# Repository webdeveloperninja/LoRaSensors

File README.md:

# Remote Monitoring Arduino Shield
## LoRa Connectivity
## Sensors
- Temperature
- Humidity
- Air Particulate
- Ambient Light

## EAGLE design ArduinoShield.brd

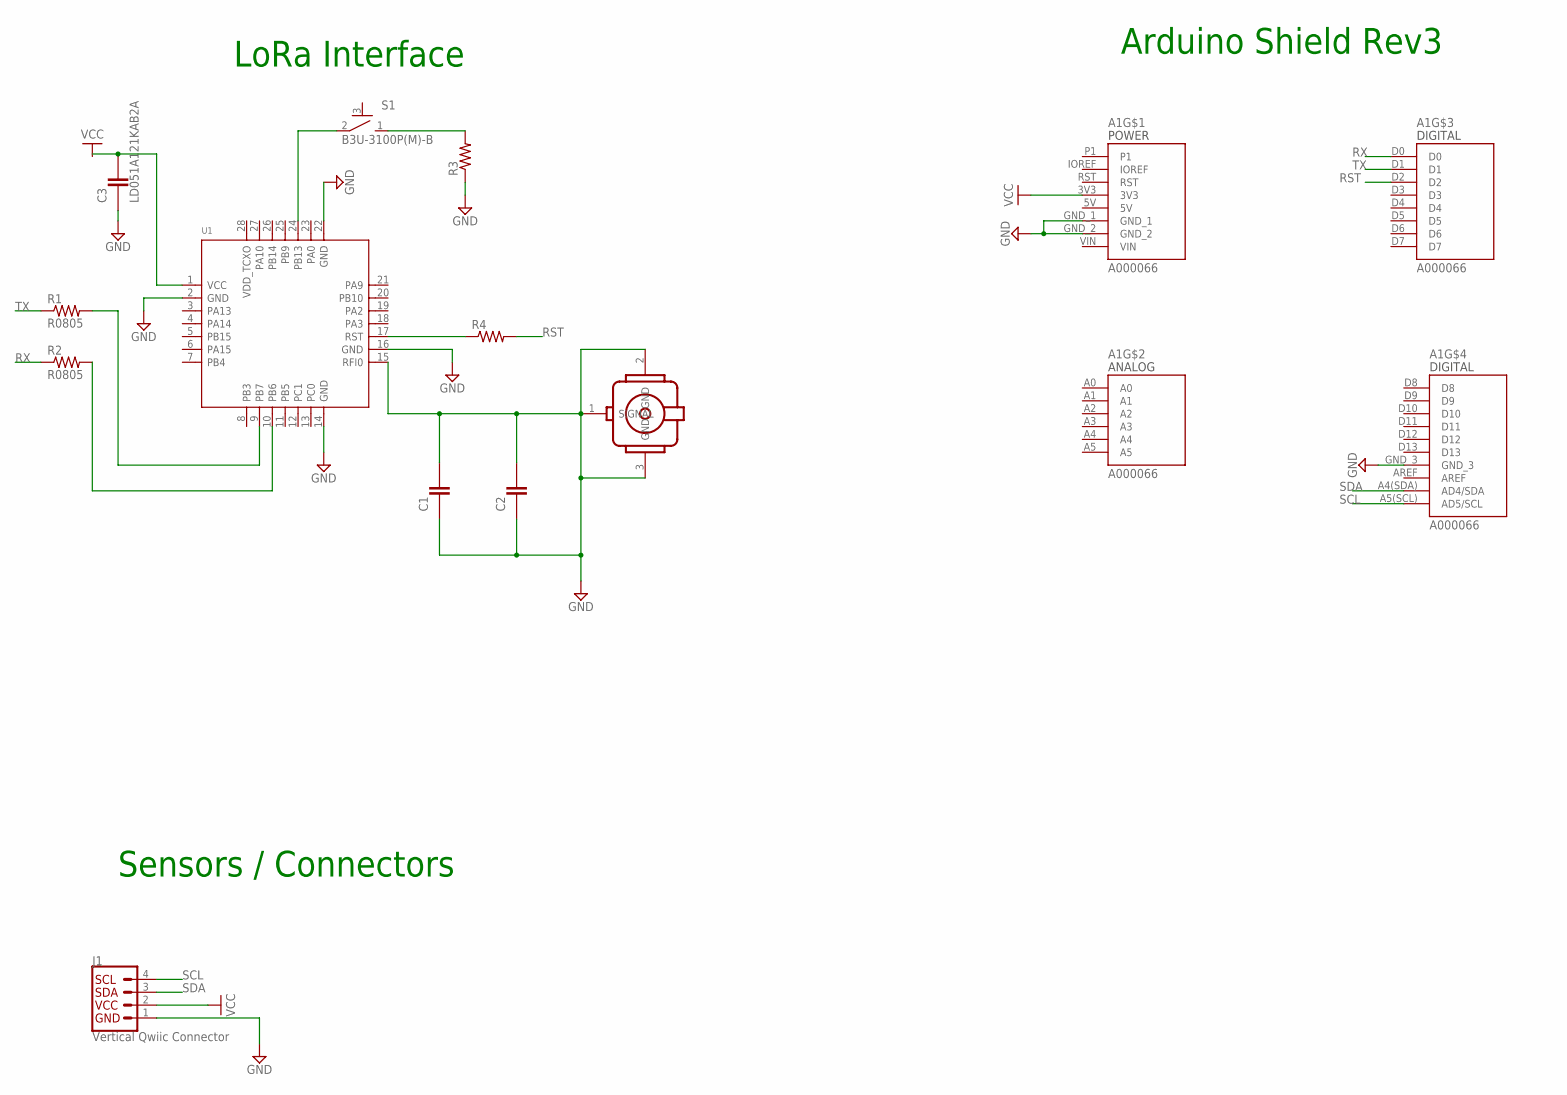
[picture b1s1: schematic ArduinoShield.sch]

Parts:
A1: A000066; ARDUINO_A000066
C1, C2, C3: LD051A121KAB2A; CAPC2012X140N
J1: Vertical Qwiic Connector; JST04_1MM_VERT
R1, R2: R0805; RESC2012X65N
R3, R4: 2-2176053-0; RESC2012X65N
S1: B3U-3100P(M)-B
U1: MODULE_LORA_E5; MODULE28P-1.25-12X12X2.5MM
U$1: U.FL-R-SMT-1(60)

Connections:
5V: A1.5V
GND: A1.GND_1, A1.GND_2, A1.GND_3, C1.1, C1.2, C2.1, C2.2, J1.1, R3.1, U1.2 (GND), U1.14 (GND), U1.15 (RFI0), U1.16 (GND), U1.22 (GND), U$1.1 (SIGNAL), U$1.2 (GND), U$1.3 (GND)
unnamed: R2.2, U1.10 (PB6)
unnamed: R1.2, U1.9 (PB7)
unnamed: R4.1, U1.17 (RST)
unnamed: S1.2 (1), U1.24 (PB13)
unnamed: R3.2, S1.1 (2)
RST: A1.D2, R4.2
RX: A1.D0, R2.1
SCL: A1.A5(SCL) (AD5/SCL), J1.4
SDA: A1.A4(SDA) (AD4/SDA), J1.3
TX: A1.D1, R1.1
VCC: A1.3V3, C3.2, J1.2, U1.1 (VCC)
VIN: A1.VIN

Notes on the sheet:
Arduino Shield Rev3
LoRa Interface
Sensors / Connectors

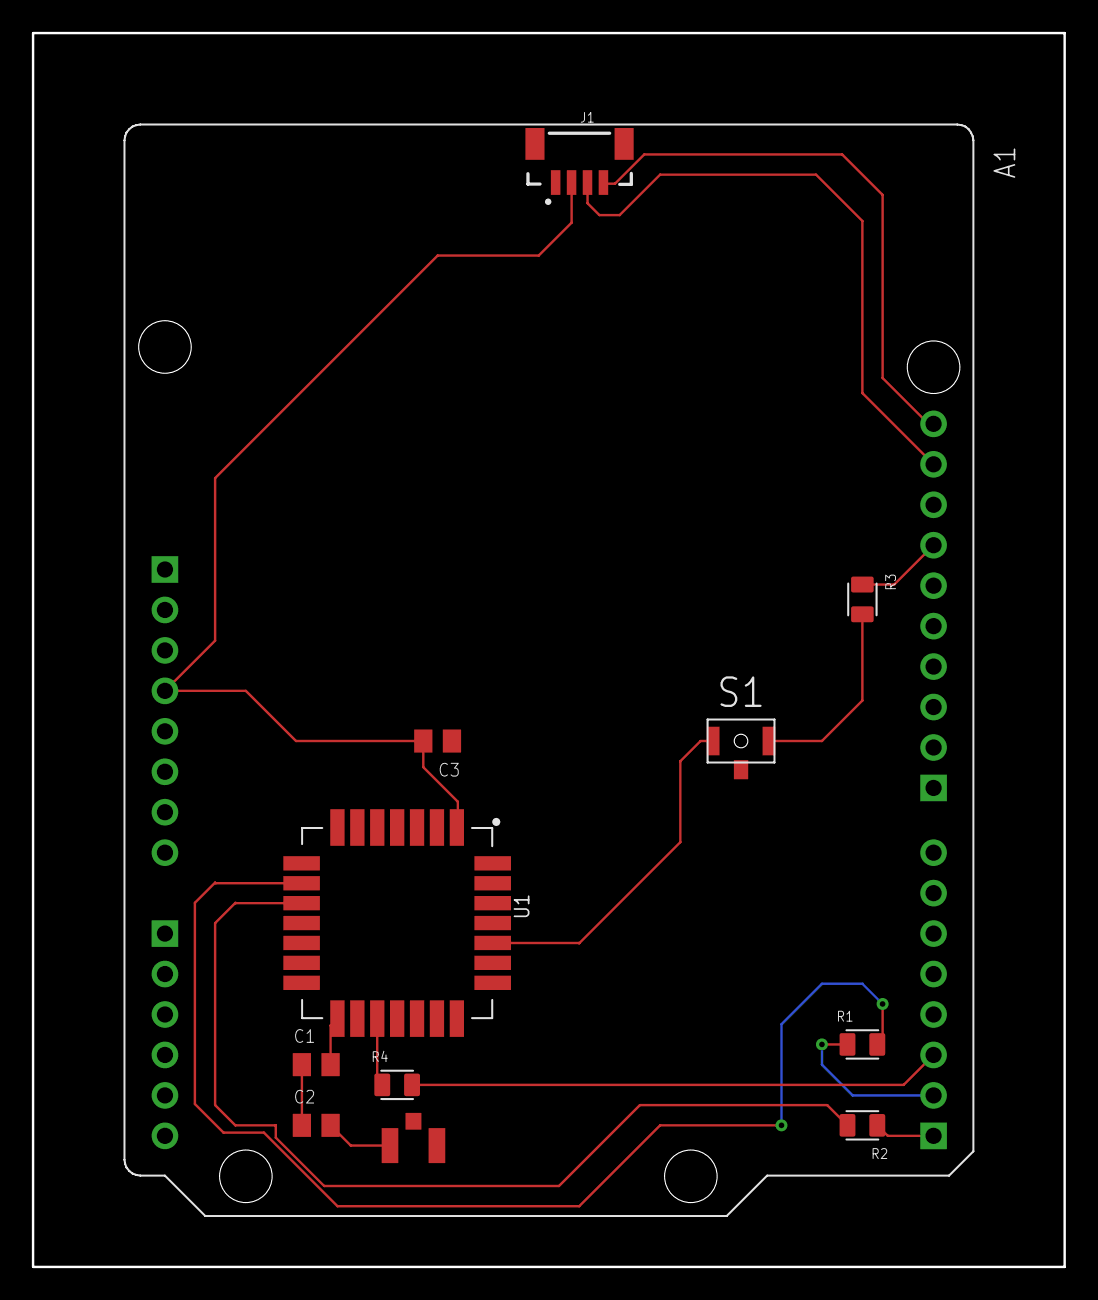
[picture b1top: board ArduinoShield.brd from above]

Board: 2 copper layers, 64.8 x 77.5 mm, 12 parts (0 on the bottom side), 12 nets.

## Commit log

2023-01-21 initial
2023-01-23 Stubbed in lora
2023-01-25 stubbed in i2c
2023-02-23 one i2C

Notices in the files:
parts and their libraries:
SparkFun-Connectors: Licensing: Creative Commons ShareAlike 4.0 International - https://creativecommons.org/licenses/by-sa/4.0
